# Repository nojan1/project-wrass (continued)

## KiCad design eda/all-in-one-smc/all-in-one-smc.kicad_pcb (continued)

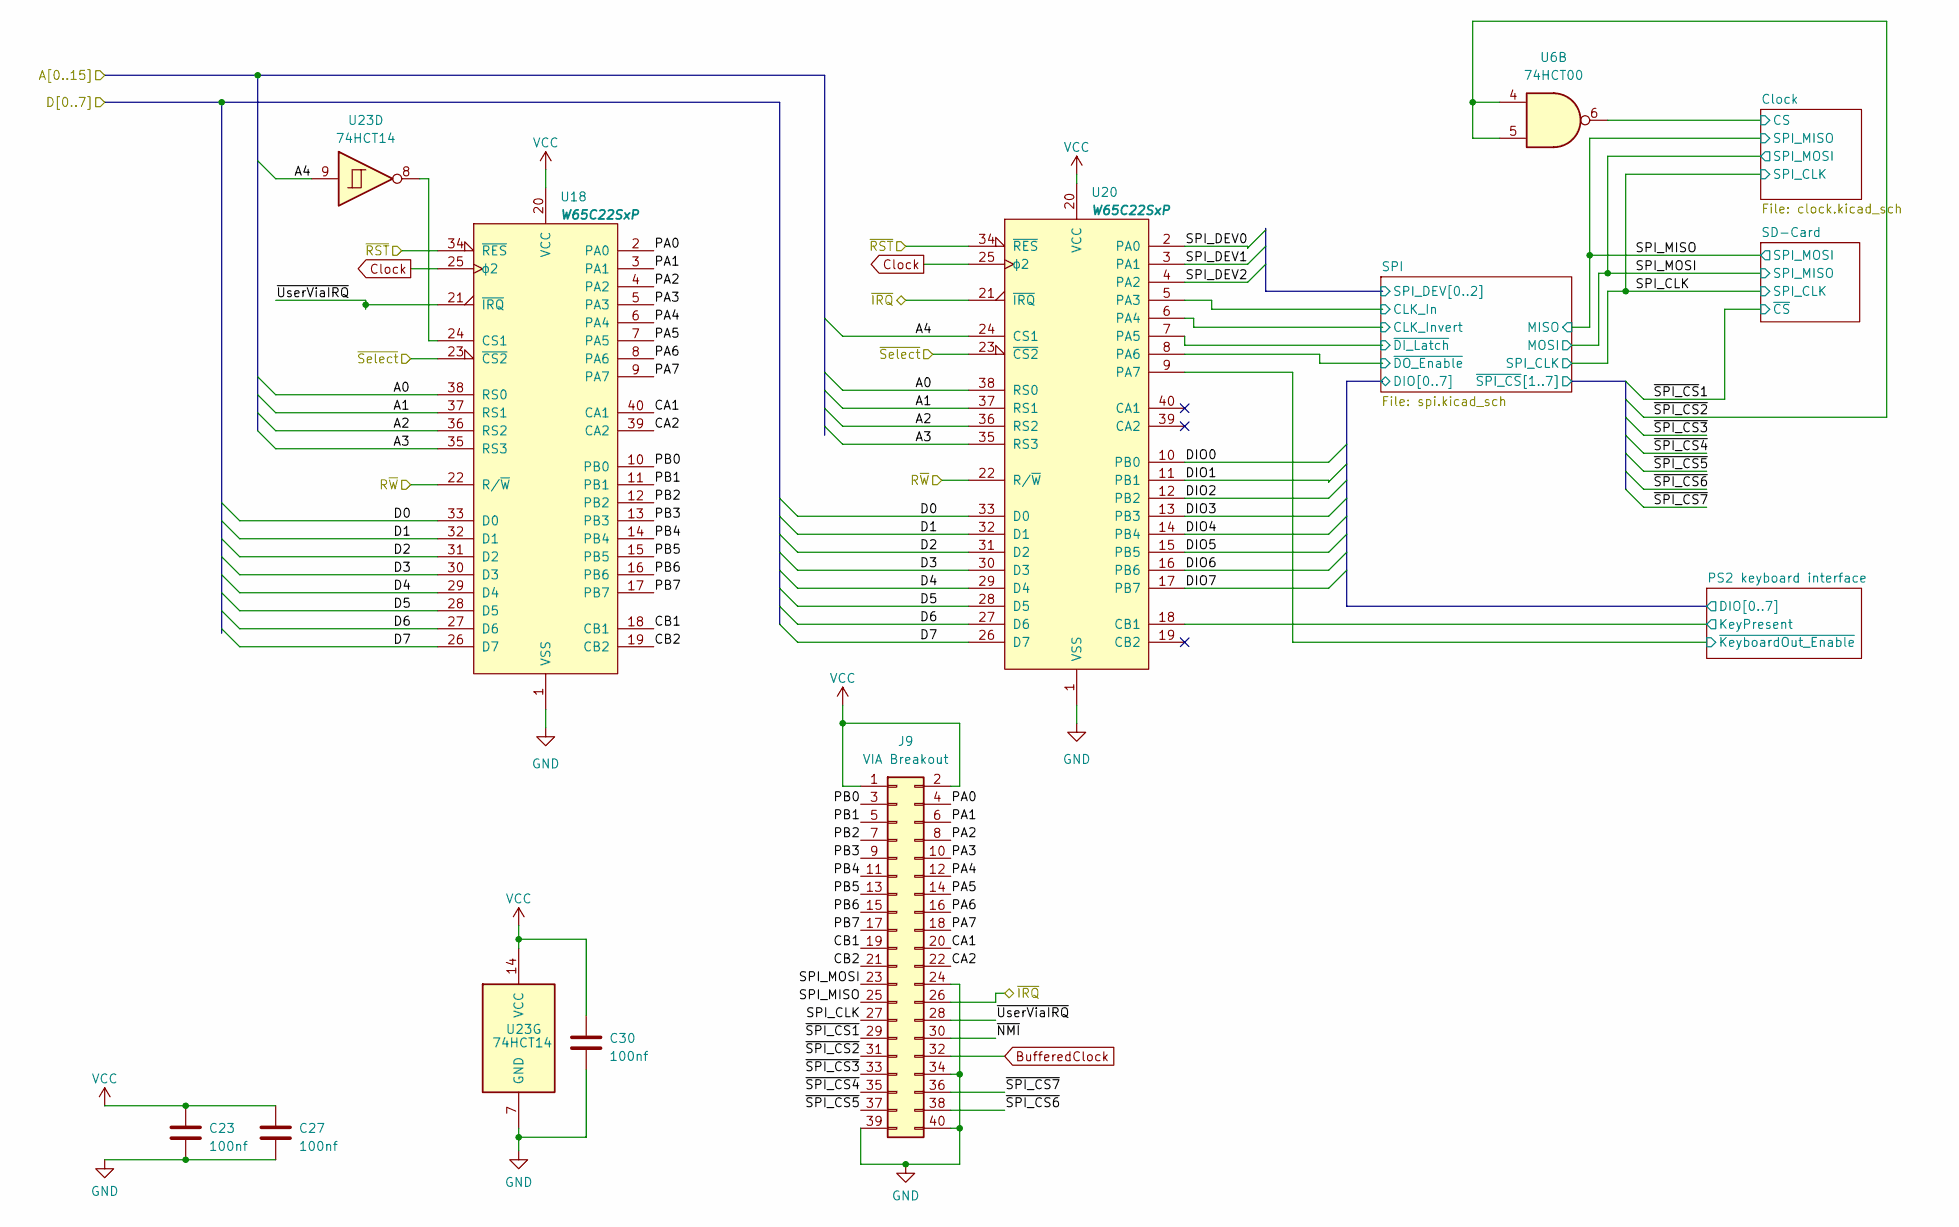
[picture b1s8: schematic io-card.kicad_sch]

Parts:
C23, C27, C30: 100nf; C_0805_2012Metric
J9: VIA Breakout; PinHeader_2x20_P2.54mm_Horizontal
U6: 74HCT00; SOIC-14_3.9x8.7mm_P1.27mm
U18, U20: W65C22SxP; PLCC-44_16.6x16.6mm_P1.27mm
U23: 74HCT14; SOIC-14_3.9x8.7mm_P1.27mm

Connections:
/A0: U18.38 (RS0), U20.38 (RS0); also elsewhere on the board
/A1: U18.37 (RS1), U20.37 (RS1); also elsewhere on the board
/A2: U18.36 (RS2), U20.36 (RS2); also elsewhere on the board
/A3: U18.35 (RS3), U20.35 (RS3); also elsewhere on the board
/A4: U20.24 (CS1), U23.9; also elsewhere on the board
/Address decode/R~W: U18.22 (R/~W), U20.22 (R/~W); also elsewhere on the board
/D0: U18.33 (D0), U20.33 (D0); also elsewhere on the board
/D1: U18.32 (D1), U20.32 (D1); also elsewhere on the board
/D2: U18.31 (D2), U20.31 (D2); also elsewhere on the board
/D3: U18.30 (D3), U20.30 (D3); also elsewhere on the board
/D4: U18.29 (D4), U20.29 (D4); also elsewhere on the board
/D5: U18.28 (D5), U20.28 (D5); also elsewhere on the board
/D6: U18.27 (D6), U20.27 (D6); also elsewhere on the board
/D7: U18.26 (D7), U20.26 (D7); also elsewhere on the board
/Expansion/IoSelect0: U18.23 (~CS2), U20.23 (~CS2); also elsewhere on the board
/Expansion/~IRQ: J9.26, U20.21 (~IRQ); also elsewhere on the board
/Expansion/~RST: U18.34 (~RES), U20.34 (~RES); also elsewhere on the board
/IO/CA1: J9.20, U18.40 (CA1)
/IO/CA2: J9.22, U18.39 (CA2)
/IO/CB1: J9.19, U18.18 (CB1)
/IO/CB2: J9.21, U18.19 (CB2)
/IO/Clock/CS: U6.6; also elsewhere on the board
/IO/PA2: J9.8, U18.4 (PA2)
/IO/PA5: J9.14, U18.7 (PA5)
/IO/PA6: J9.16, U18.8 (PA6)
/IO/PA7: J9.18, U18.9 (PA7)
/IO/PB3: J9.9, U18.13 (PB3)
/IO/PB6: J9.15, U18.16 (PB6)
/IO/PB7: J9.17, U18.17 (PB7)
/IO/PS2 keyboard interface/DIO0: U20.10 (PB0); also elsewhere on the board
/IO/PS2 keyboard interface/DIO1: U20.11 (PB1); also elsewhere on the board
/IO/PS2 keyboard interface/DIO2: U20.12 (PB2); also elsewhere on the board
/IO/PS2 keyboard interface/DIO3: U20.13 (PB3); also elsewhere on the board
/IO/PS2 keyboard interface/DIO4: U20.14 (PB4); also elsewhere on the board
/IO/PS2 keyboard interface/DIO5: U20.15 (PB5); also elsewhere on the board
/IO/PS2 keyboard interface/DIO6: U20.16 (PB6); also elsewhere on the board
/IO/PS2 keyboard interface/DIO7: U20.17 (PB7); also elsewhere on the board
/IO/PS2 keyboard interface/KeyPresent: U20.18 (CB1); also elsewhere on the board
/IO/PS2 keyboard interface/~KeyboardOut_Enable: U20.9 (PA7)
/IO/SPI/CLK_Invert: U20.6 (PA4); also elsewhere on the board
/IO/SPI/SPI_DEV0: U20.2 (PA0); also elsewhere on the board
/IO/SPI/SPI_DEV1: U20.3 (PA1); also elsewhere on the board
/IO/SPI/SPI_DEV2: U20.4 (PA2); also elsewhere on the board
/IO/SPI/~DI_Latch: U20.7 (PA5); also elsewhere on the board
/IO/SPI/~DO_Enable: U20.8 (PA6); also elsewhere on the board
/IO/SPI_CLK: J9.27, U20.5 (PA3); also elsewhere on the board
/IO/SPI_MISO: J9.25; also elsewhere on the board
/IO/SPI_MOSI: J9.23; also elsewhere on the board
/IO/~NMI: J9.30
/IO/~SPI_CS1: J9.29
/IO/~SPI_CS2: J9.31, U6.4, U6.5
/IO/~SPI_CS3: J9.33
/IO/~SPI_CS4: J9.35
/IO/~SPI_CS5: J9.37
/IO/~SPI_CS6: J9.38
/IO/~SPI_CS7: J9.36
/IO/~UserViaIRQ: J9.28, U18.21 (~IRQ)
BufferedClock: J9.32
Clock: U18.25 (ϕ2), U20.25 (ϕ2); also elsewhere on the board
unnamed: U18.24 (CS1), U23.8

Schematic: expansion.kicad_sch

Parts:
C18: 1u; CP_Elec_5x3
C20: 100n; C_0805_2012Metric
J6: Expansion; PinHeader_2x25_P2.54mm_Vertical
R7, R9, R10: 10k; R_0805_2012Metric
U13: 74HCT138; SOIC-16_3.9x9.9mm_P1.27mm

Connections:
/A0: J6.5; also elsewhere on the board
/A1: J6.7; also elsewhere on the board
/A2: J6.9; also elsewhere on the board
/A3: J6.11; also elsewhere on the board
/A4: J6.13; also elsewhere on the board
/A5: J6.15; also elsewhere on the board
/A6: J6.17, U13.1 (A0); also elsewhere on the board
/A7: J6.19, U13.2 (A1); also elsewhere on the board
/A8: J6.21, U13.3 (A2); also elsewhere on the board
/A9: J6.23; also elsewhere on the board
/A10: J6.25; also elsewhere on the board
/A11: J6.27; also elsewhere on the board
/A12: J6.29; also elsewhere on the board
/A13: J6.31; also elsewhere on the board
/A14: J6.33; also elsewhere on the board
/A15: J6.35; also elsewhere on the board
/Address decode/R~W: J6.41; also elsewhere on the board
/Address decode/~Io1Cs: U13.4 (E1), U13.5 (E2); also elsewhere on the board
/D0: J6.4; also elsewhere on the board
/D1: J6.6; also elsewhere on the board
/D2: J6.8; also elsewhere on the board
/D3: J6.10; also elsewhere on the board
/D4: J6.12; also elsewhere on the board
/D5: J6.14; also elsewhere on the board
/D6: J6.16; also elsewhere on the board
/D7: J6.18; also elsewhere on the board
/Expansion/IoSelect0: J6.22, U13.15 (O0); also elsewhere on the board
/Expansion/IoSelect1: J6.24, U13.14 (O1); also elsewhere on the board
/Expansion/IoSelect2: J6.26, U13.13 (O2)
/Expansion/IoSelect3: J6.28, U13.12 (O3); also elsewhere on the board
/Expansion/IoSelect4: J6.30, U13.11 (O4)
/Expansion/IoSelect5: J6.32, U13.10 (O5)
/Expansion/IoSelect6: J6.34, U13.9 (O6)
/Expansion/IoSelect7: J6.36, U13.7 (O7)
/Expansion/~DMA: J6.43, R7.2; also elsewhere on the board
/Expansion/~ExtRomCS: J6.48
/Expansion/~IRQ: J6.44, R10.2; also elsewhere on the board
/Expansion/~NMI: J6.42, R9.2; also elsewhere on the board
/Expansion/~RST: J6.40; also elsewhere on the board
Audio_GND: J6.47
Audio_L: J6.49
Audio_R: J6.45
Clock: J6.39; also elsewhere on the board

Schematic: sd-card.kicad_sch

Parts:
C44: 100nf; C_0805_2012Metric
C45: 100nf; CP_Elec_3x5.3
J11: SD-Card module; PinHeader_1x08_P2.54mm_Vertical
J12: SD_Card; SD_Kyocera_145638109511859+; not fitted
JP6: SD-Card voltage select; SolderJumper-3_P1.3mm_Open_Pad1.0x1.5mm
Q2, Q3, Q4, Q5: 2N7002; SOT-23
R30, R31, R32, R33, R34, R35, R36, R37: 10k; R_0805_2012Metric
R38: 370R; R_0805_2012Metric
R39: 220R; R_0805_2012Metric
U32: LM317L; SOT-223-3_TabPin2

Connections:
/IO/SPI/~SPI_CS1: Q2.3 (D), R34.2
/IO/SPI_CLK: Q4.3 (D), R36.2; also elsewhere on the board
/IO/SPI_MISO: Q3.3 (D), R35.2; also elsewhere on the board
/IO/SPI_MOSI: Q5.3 (D), R37.2; also elsewhere on the board
unnamed: J11.8, JP6.2 (C)
unnamed: R38.2, R39.1, U32.1 (ADJ)

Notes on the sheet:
VOUT = 1.25 * ( 1 + R2/R1 )
3.3 ~ 1.25 * ( 1 + 370/220 )

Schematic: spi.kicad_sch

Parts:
C38, C40, C41, C42, C43: 100nf; C_0805_2012Metric
J13: CS_Invert_Selection; PinHeader_2x03_P2.54mm_Horizontal
R40, R41, R42: 10k; R_0805_2012Metric
U23: 74HCT14; SOIC-14_3.9x8.7mm_P1.27mm
U24: 74HCT86; SOIC-14_3.9x8.7mm_P1.27mm
U26: 74HCT595; SOIC-16_3.9x9.9mm_P1.27mm
U27: 74HCT165; SOIC-16_3.9x9.9mm_P1.27mm
U31: 74HCT138; SOIC-16_3.9x9.9mm_P1.27mm

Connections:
/A4: U23.9; also elsewhere on the board
/IO/PS2 keyboard interface/DIO0: U26.7 (QH), U27.6 (D7); also elsewhere on the board
/IO/PS2 keyboard interface/DIO1: U26.6 (QG), U27.5 (D6); also elsewhere on the board
/IO/PS2 keyboard interface/DIO2: U26.5 (QF), U27.4 (D5); also elsewhere on the board
/IO/PS2 keyboard interface/DIO3: U26.4 (QE), U27.3 (D4); also elsewhere on the board
/IO/PS2 keyboard interface/DIO4: U26.3 (QD), U27.14 (D3); also elsewhere on the board
/IO/PS2 keyboard interface/DIO5: U26.2 (QC), U27.13 (D2); also elsewhere on the board
/IO/PS2 keyboard interface/DIO6: U26.1 (QB), U27.12 (D1); also elsewhere on the board
/IO/PS2 keyboard interface/DIO7: U26.15 (QA), U27.11 (D0); also elsewhere on the board
/IO/PS2 keyboard interface/KeyPresent: U23.6; also elsewhere on the board
/IO/PS2 keyboard interface/~KeyboardClk: U23.4; also elsewhere on the board
/IO/SPI/ ~SPI_CS1: U31.14 (O1)
/IO/SPI/CLK_Invert: U24.2; also elsewhere on the board
/IO/SPI/Conditioned_CLK: U23.13, U24.3, U26.11 (SRCLK)
/IO/SPI/SPI_DEV0: U31.1 (A0); also elsewhere on the board
/IO/SPI/SPI_DEV1: U31.2 (A1); also elsewhere on the board
/IO/SPI/SPI_DEV2: U31.3 (A2); also elsewhere on the board
/IO/SPI/~Conditioned_CLK: U23.12, U27.2 (CP)
/IO/SPI/~DI_Latch: U27.1 (~PL); also elsewhere on the board
/IO/SPI/~DO_Enable: U23.11, U26.13 (~OE); also elsewhere on the board
/IO/SPI/~SPI_CS2: U31.13 (O2)
/IO/SPI/~SPI_CS3: U31.12 (O3)
/IO/SPI/~SPI_CS4: U31.11 (O4)
/IO/SPI/~SPI_CS5: U24.6
/IO/SPI/~SPI_CS6: U24.8
/IO/SPI/~SPI_CS7: U24.11
/IO/SPI_CLK: U24.1; also elsewhere on the board
/IO/SPI_MISO: U26.14 (SER); also elsewhere on the board
/IO/SPI_MOSI: U27.9 (Q7); also elsewhere on the board
unnamed 158: U23.2; also elsewhere on the board
unnamed 159: U23.5; also elsewhere on the board
unnamed 165: U23.1, U23.3; also elsewhere on the board
unnamed: J13.1, R40.1, U24.13
unnamed: J13.3, R41.1, U24.10
unnamed: J13.5, R42.1, U24.5
unnamed 199: U23.8; also elsewhere on the board
unnamed: U23.10, U26.12 (RCLK)
unnamed: U24.4, U31.10 (O5)
unnamed: U24.9, U31.9 (O6)
unnamed: U24.12, U31.7 (O7)

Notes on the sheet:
Should these be swapped?

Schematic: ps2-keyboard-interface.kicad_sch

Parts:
C36, C37, C39: 100nf; C_0805_2012Metric
D3: 1N457; D_0805_2012Metric
J10: PS2; Connector_Mini-DIN_Female_6Pin_2rows
R29: 33k; R_0805_2012Metric
U23: 74HCT14; SOIC-14_3.9x8.7mm_P1.27mm
U29, U30: 74HCT595; SOIC-16_3.9x9.9mm_P1.27mm

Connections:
/IO/PS2 keyboard interface/DIO0: U29.1 (QB); also elsewhere on the board
/IO/PS2 keyboard interface/DIO1: U29.2 (QC); also elsewhere on the board
/IO/PS2 keyboard interface/DIO2: U29.3 (QD); also elsewhere on the board
/IO/PS2 keyboard interface/DIO3: U29.4 (QE); also elsewhere on the board
/IO/PS2 keyboard interface/DIO4: U29.5 (QF); also elsewhere on the board
/IO/PS2 keyboard interface/DIO5: U29.6 (QG); also elsewhere on the board
/IO/PS2 keyboard interface/DIO6: U29.7 (QH); also elsewhere on the board
/IO/PS2 keyboard interface/KeyPresent: U23.6, U29.12 (RCLK), U30.12 (RCLK); also elsewhere on the board
/IO/PS2 keyboard interface/KeyboardBit7: U30.15 (QA)
/IO/PS2 keyboard interface/KeyboardData: J10.1, U29.14 (SER)
/IO/PS2 keyboard interface/~KeyboardClk: U23.4, U29.11 (SRCLK), U30.11 (SRCLK)
/IO/PS2 keyboard interface/~PS2ShiftOE: U29.13 (~OE), U30.13 (~OE); also elsewhere on the board
unnamed: D3.2 (A), R29.2, U23.2
unnamed: C39.1, D3.1 (K), R29.1, U23.5
unnamed: J10.5, U23.1, U23.3
unnamed: U29.9 (QH'), U30.14 (SER)

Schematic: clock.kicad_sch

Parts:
BT1: CR2032; Battery_Panasonic_CR2032-HFN_Horizontal_CircularHoles
C46, C47: 6pf; C_0805_2012Metric
U100: DS1306; TSSOP-20_4.4x5mm_P0.4mm
Y3: 32.768kHz; Crystal_C26-LF_D2.1mm_L6.5mm_Vertical

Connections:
/IO/Clock/CS: U100.12 (CE); also elsewhere on the board
/IO/SPI_CLK: U100.14 (SCLK); also elsewhere on the board
/IO/SPI_MISO: U100.16 (SDO); also elsewhere on the board
/IO/SPI_MOSI: U100.15 (SDI); also elsewhere on the board
unnamed: BT1.1 (+), U100.2 (VBAT)
unnamed: C46.2, U100.3 (X1), Y3.2
unnamed: C47.2, U100.5 (X2), Y3.1

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
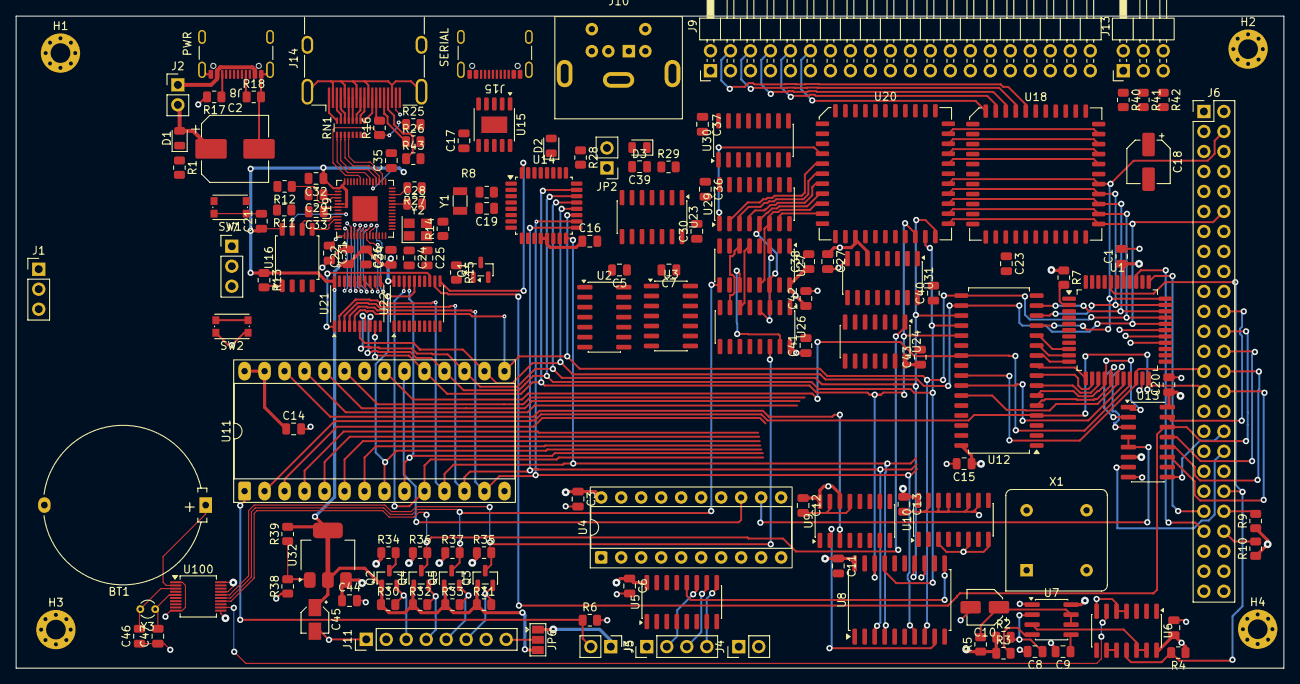
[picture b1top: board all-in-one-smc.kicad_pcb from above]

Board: 4 copper layers, 161.1 x 82.9 mm, 150 parts (0 on the bottom side), 210 nets.

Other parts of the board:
JP2: Enable PS2 Output; PinHeader_1x02_P2.54mm_Vertical
R28: 10k; R_0805_2012Metric

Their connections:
/IO/PS2 keyboard interface/~PS2ShiftOE: JP2.1 (A), R28.2; also elsewhere on the board

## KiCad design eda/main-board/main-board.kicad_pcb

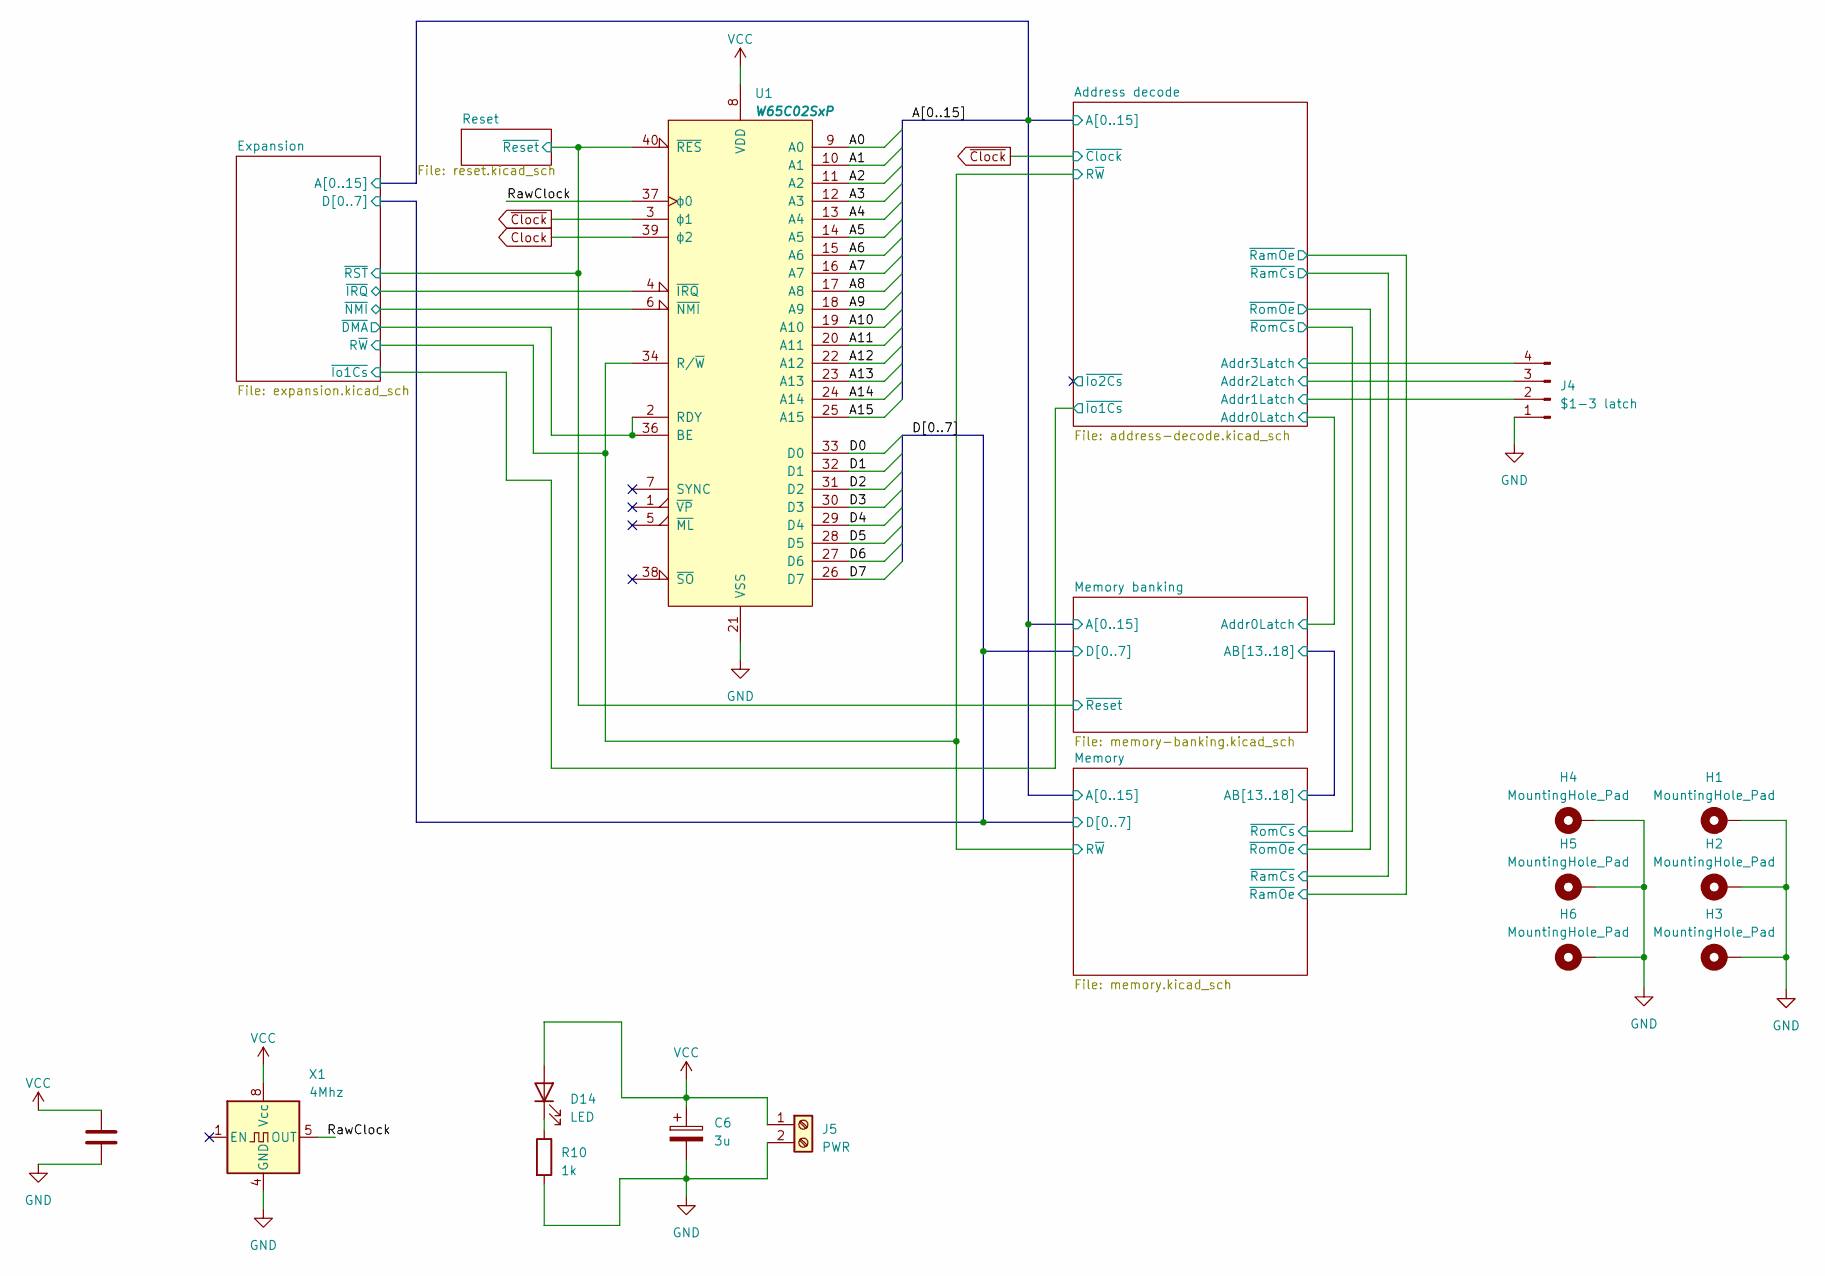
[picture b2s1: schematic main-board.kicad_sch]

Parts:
C4: 100n; C_Disc_D3.8mm_W2.6mm_P2.50mm
C6: 3u; CP_Radial_D8.0mm_P3.50mm
D14: LED; LED_D3.0mm
H1, H2, H3, H4, H5, H6: MountingHole_Pad; MountingHole_2.5mm_Pad_Via
J4: $1-3 latch; PinHeader_1x04_P2.54mm_Vertical
J5: PWR; TerminalBlock_Altech_AK300-2_P5.00mm
R10: 1k; R_Axial_DIN0207_L6.3mm_D2.5mm_P7.62mm_Horizontal
U1: W65C02SxP; DIP-40_W15.24mm
X1: 4Mhz; Oscillator_DIP-8

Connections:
/A0: U1.9 (A0); also elsewhere on the board
/A1: U1.10 (A1); also elsewhere on the board
/A2: U1.11 (A2); also elsewhere on the board
/A3: U1.12 (A3); also elsewhere on the board
/A4: U1.13 (A4); also elsewhere on the board
/A5: U1.14 (A5); also elsewhere on the board
/A6: U1.15 (A6); also elsewhere on the board
/A7: U1.16 (A7); also elsewhere on the board
/A8: U1.17 (A8); also elsewhere on the board
/A9: U1.18 (A9); also elsewhere on the board
/A10: U1.19 (A10); also elsewhere on the board
/A11: U1.20 (A11); also elsewhere on the board
/A12: U1.22 (A12); also elsewhere on the board
/A13: U1.23 (A13); also elsewhere on the board
/A14: U1.24 (A14); also elsewhere on the board
/A15: U1.25 (A15); also elsewhere on the board
/Address decode/Addr1Latch: J4.2; also elsewhere on the board
/Address decode/Addr2Latch: J4.3; also elsewhere on the board
/Address decode/Addr3Latch: J4.4; also elsewhere on the board
/Address decode/R~W: U1.34 (R/~W); also elsewhere on the board
/D0: U1.33 (D0); also elsewhere on the board
/D1: U1.32 (D1); also elsewhere on the board
/D2: U1.31 (D2); also elsewhere on the board
/D3: U1.30 (D3); also elsewhere on the board
/D4: U1.29 (D4); also elsewhere on the board
/D5: U1.28 (D5); also elsewhere on the board
/D6: U1.27 (D6); also elsewhere on the board
/D7: U1.26 (D7); also elsewhere on the board
/Expansion/~DMA: U1.2 (RDY), U1.36 (BE); also elsewhere on the board
/Expansion/~IRQ: U1.4 (~IRQ); also elsewhere on the board
/Expansion/~NMI: U1.6 (~NMI); also elsewhere on the board
/Expansion/~RST: U1.40 (~RES); also elsewhere on the board
/RawClock: U1.37 (ϕ0), X1.5 (OUT)
Clock: U1.39 (ϕ2); also elsewhere on the board
GND: C4.2, C6.2, H1.1, H2.1, H3.1, H4.1, H5.1, H6.1, J4.1, J5.2, R10.2, U1.21 (VSS), X1.4 (GND); also elsewhere on the board
unnamed: D14.1 (K), R10.1
VCC: C4.1, C6.1, D14.2 (A), J5.1, U1.8 (VDD), X1.8 (Vcc); also elsewhere on the board
~Clock: U1.3 (ϕ1); also elsewhere on the board

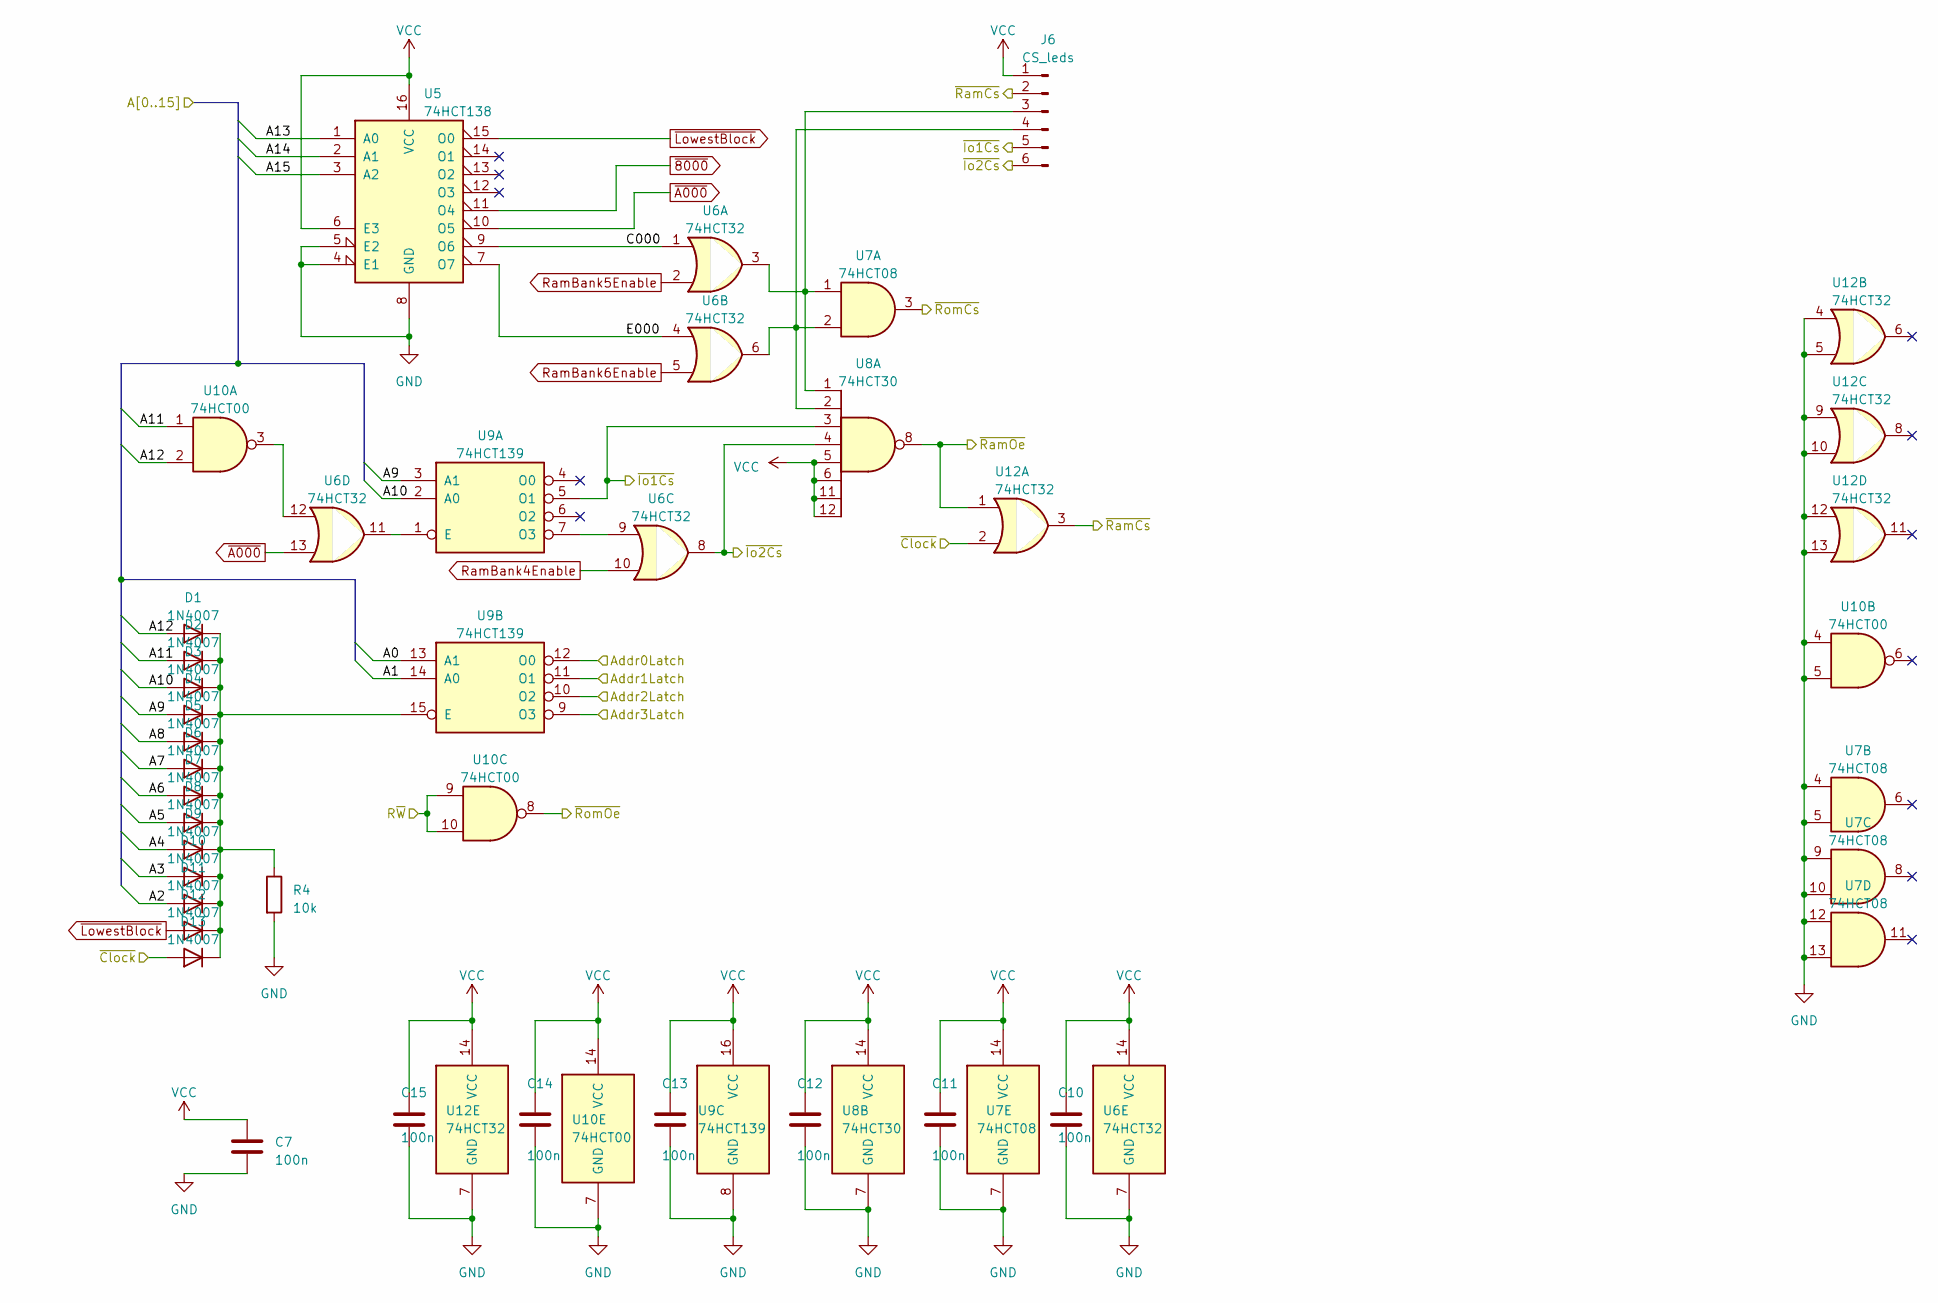
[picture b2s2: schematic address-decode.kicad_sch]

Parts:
C7, C10, C11, C12, C13, C14, C15: 100n; C_Disc_D3.8mm_W2.6mm_P2.50mm
D1, D2, D3, D4, D5, D6, D7, D8, D9, D10, D11, D12, D13: 1N4007; D_DO-41_SOD81_P7.62mm_Horizontal
J6: CS_leds; PinHeader_1x06_P2.54mm_Vertical
R4: 10k; R_Axial_DIN0207_L6.3mm_D2.5mm_P7.62mm_Horizontal
U5: 74HCT138; DIP-16_W7.62mm
U6, U12: 74HCT32; DIP-14_W7.62mm
U7: 74HCT08; DIP-14_W7.62mm
U8: 74HCT30; DIP-14_W7.62mm
U9: 74HCT139; DIP-16_W7.62mm
U10: 74HCT00; DIP-14_W7.62mm

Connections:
/A0: U9.13 (A1); also elsewhere on the board
/A1: U9.14 (A0); also elsewhere on the board
/A2: D11.2 (A); also elsewhere on the board
/A3: D10.2 (A); also elsewhere on the board
/A4: D9.2 (A); also elsewhere on the board
/A5: D8.2 (A); also elsewhere on the board
/A6: D7.2 (A); also elsewhere on the board
/A7: D6.2 (A); also elsewhere on the board
/A8: D5.2 (A); also elsewhere on the board
/A9: D4.2 (A), U9.3 (A1); also elsewhere on the board
/A10: D3.2 (A), U9.2 (A0); also elsewhere on the board
/A11: D2.2 (A), U10.1; also elsewhere on the board
/A12: D1.2 (A), U10.2; also elsewhere on the board
/A13: U5.1 (A0); also elsewhere on the board
/A14: U5.2 (A1); also elsewhere on the board
/A15: U5.3 (A2); also elsewhere on the board
/Address decode/Addr0Latch: U9.12 (O0); also elsewhere on the board
/Address decode/Addr1Latch: U9.11 (O1); also elsewhere on the board
/Address decode/Addr2Latch: U9.10 (O2); also elsewhere on the board
/Address decode/Addr3Latch: U9.9 (O3); also elsewhere on the board
/Address decode/C000: U5.9 (O6), U6.1
/Address decode/E000: U5.7 (O7), U6.4
/Address decode/R~W: U10.9, U10.10; also elsewhere on the board
/Address decode/~Io1Cs: J6.5, U8.3, U9.5 (O1); also elsewhere on the board
/Address decode/~Io2Cs: J6.6, U6.8, U8.4
/Address decode/~RamCs: J6.2, U12.3; also elsewhere on the board
/Address decode/~RamOe: U8.8, U12.1; also elsewhere on the board
/Address decode/~RomCs: U7.3; also elsewhere on the board
/Address decode/~RomOe: U10.8; also elsewhere on the board
GND: C7.2, C10.2, C11.2, C12.2, C13.2, C14.2, C15.2, R4.2, U5.4 (E1), U5.5 (E2), U5.8 (GND), U6.7 (GND), U7.4, U7.5, U7.7 (GND), U7.9, U7.10, U7.12, U7.13, U8.7 (GND), U9.8 (GND), U10.4, U10.5, U10.7 (GND), U12.4, U12.5, U12.7 (GND), U12.9, U12.10, U12.12, U12.13; also elsewhere on the board
unnamed: D1.1 (K), D2.1 (K), D3.1 (K), D4.1 (K), D5.1 (K), D6.1 (K), D7.1 (K), D8.1 (K), D9.1 (K), D10.1 (K), D11.1 (K), D12.1 (K), D13.1 (K), R4.1, U9.15 (E)
unnamed: J6.3, U6.3, U7.1, U8.1
unnamed: J6.4, U6.6, U7.2, U8.2
unnamed: U6.11, U9.1 (E)
unnamed: U6.9, U9.7 (O3)
unnamed: U6.12, U10.3
RamBank4Enable: U6.10; also elsewhere on the board
RamBank5Enable: U6.2; also elsewhere on the board
RamBank6Enable: U6.5; also elsewhere on the board
VCC: C7.1, C10.1, C11.1, C12.1, C13.1, C14.1, C15.1, J6.1, U5.6 (E3), U5.16 (VCC), U6.14 (VCC), U7.14 (VCC), U8.5, U8.6, U8.11, U8.12, U8.14 (VCC), U9.16 (VCC), U10.14 (VCC), U12.14 (VCC); also elsewhere on the board
~8000: U5.11 (O4); also elsewhere on the board
~A000: U5.10 (O5), U6.13
~Clock: D13.2 (A), U12.2; also elsewhere on the board
~LowestBlock: D12.2 (A), U5.15 (O0)

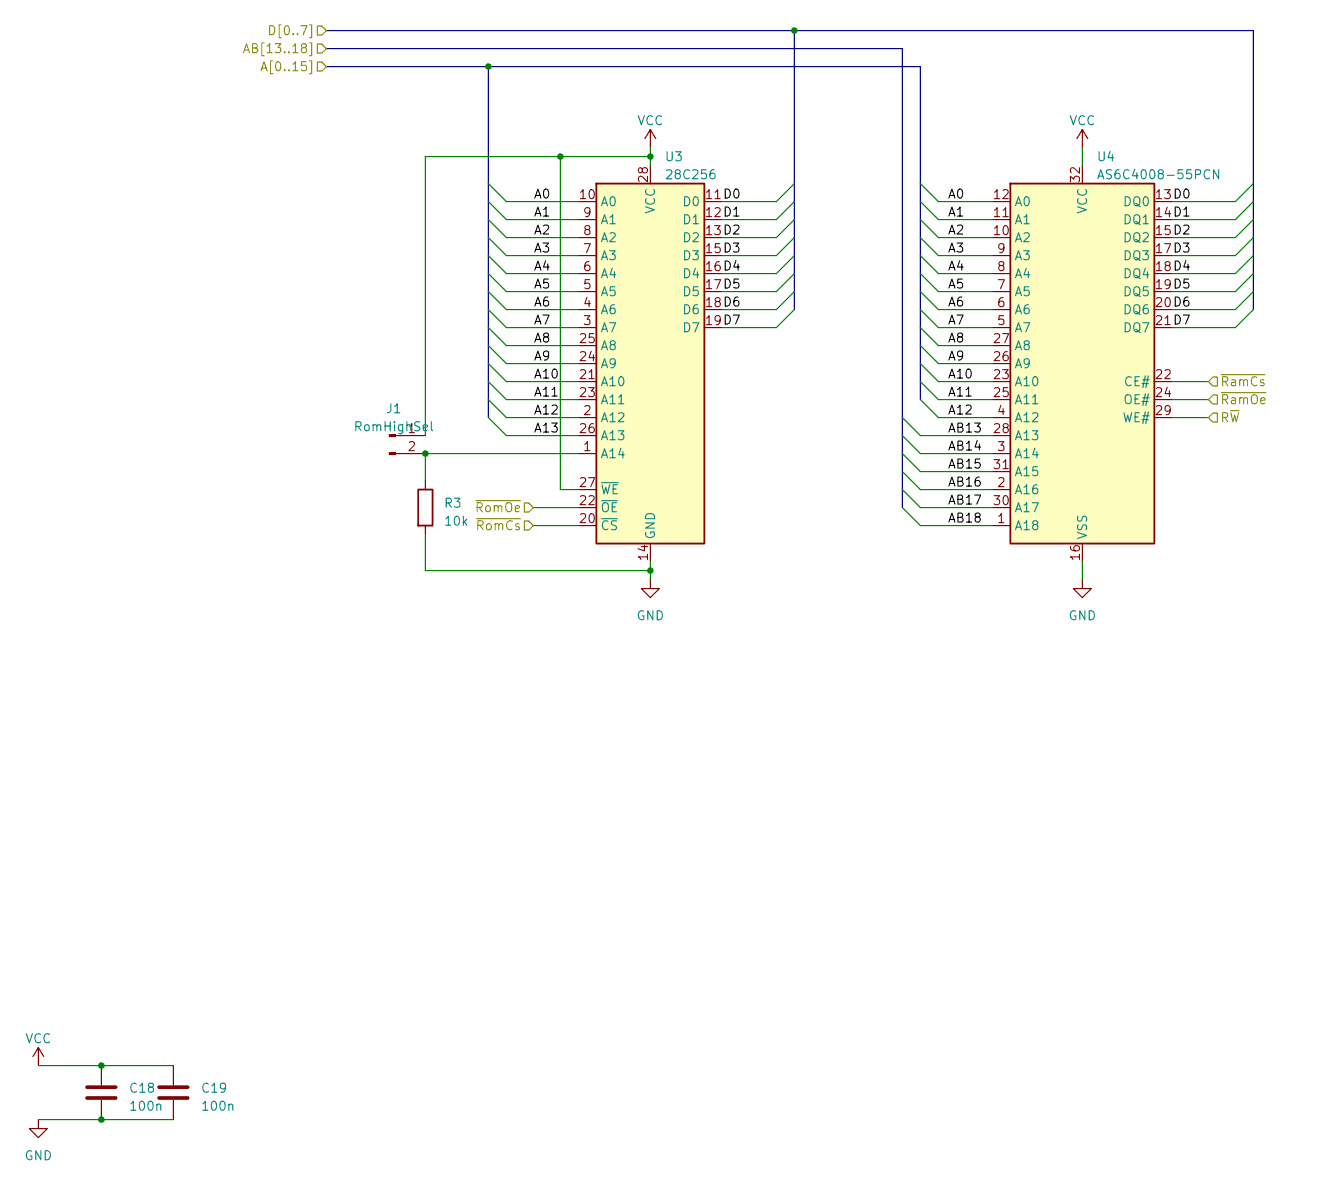
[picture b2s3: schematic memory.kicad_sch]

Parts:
C18, C19: 100n; C_Disc_D3.8mm_W2.6mm_P2.50mm
J1: RomHighSel; PinHeader_1x02_P2.54mm_Vertical
R3: 10k; R_Axial_DIN0207_L6.3mm_D2.5mm_P7.62mm_Horizontal
U3: 28C256; DIP_Socket-28_W11.9_W12.7_W15.24_W17.78_W18.5_3M_228-1277-0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
U4: AS6C4008-55PCN; DIP-32_W15.24mm

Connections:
/A0: U3.10 (A0), U4.12 (A0); also elsewhere on the board
/A1: U3.9 (A1), U4.11 (A1); also elsewhere on the board
/A2: U3.8 (A2), U4.10 (A2); also elsewhere on the board
/A3: U3.7 (A3), U4.9 (A3); also elsewhere on the board
/A4: U3.6 (A4), U4.8 (A4); also elsewhere on the board
/A5: U3.5 (A5), U4.7 (A5); also elsewhere on the board
/A6: U3.4 (A6), U4.6 (A6); also elsewhere on the board
/A7: U3.3 (A7), U4.5 (A7); also elsewhere on the board
/A8: U3.25 (A8), U4.27 (A8); also elsewhere on the board
/A9: U3.24 (A9), U4.26 (A9); also elsewhere on the board
/A10: U3.21 (A10), U4.23 (A10); also elsewhere on the board
/A11: U3.23 (A11), U4.25 (A11); also elsewhere on the board
/A12: U3.2 (A12), U4.4 (A12); also elsewhere on the board
/A13: U3.26 (A13); also elsewhere on the board
/Address decode/R~W: U4.29 (WE#); also elsewhere on the board
/Address decode/~RamCs: U4.22 (CE#); also elsewhere on the board
/Address decode/~RamOe: U4.24 (OE#); also elsewhere on the board
/Address decode/~RomCs: U3.20 (~CS); also elsewhere on the board
/Address decode/~RomOe: U3.22 (~OE); also elsewhere on the board
/D0: U3.11 (D0), U4.13 (DQ0); also elsewhere on the board
/D1: U3.12 (D1), U4.14 (DQ1); also elsewhere on the board
/D2: U3.13 (D2), U4.15 (DQ2); also elsewhere on the board
/D3: U3.15 (D3), U4.17 (DQ3); also elsewhere on the board
/D4: U3.16 (D4), U4.18 (DQ4); also elsewhere on the board
/D5: U3.17 (D5), U4.19 (DQ5); also elsewhere on the board
/D6: U3.18 (D6), U4.20 (DQ6); also elsewhere on the board
/D7: U3.19 (D7), U4.21 (DQ7); also elsewhere on the board
/Memory banking/AB13: U4.28 (A13); also elsewhere on the board
/Memory banking/AB14: U4.3 (A14); also elsewhere on the board
/Memory banking/AB15: U4.31 (A15); also elsewhere on the board
/Memory banking/AB16: U4.2 (A16); also elsewhere on the board
/Memory banking/AB17: U4.30 (A17); also elsewhere on the board
/Memory banking/AB18: U4.1 (A18); also elsewhere on the board
GND: C18.2, C19.2, R3.2, U3.14 (GND), U4.16 (VSS); also elsewhere on the board
unnamed: J1.2, R3.1, U3.1 (A14)
VCC: C18.1, C19.1, J1.1, U3.27 (~WE), U3.28 (VCC), U4.32 (VCC); also elsewhere on the board

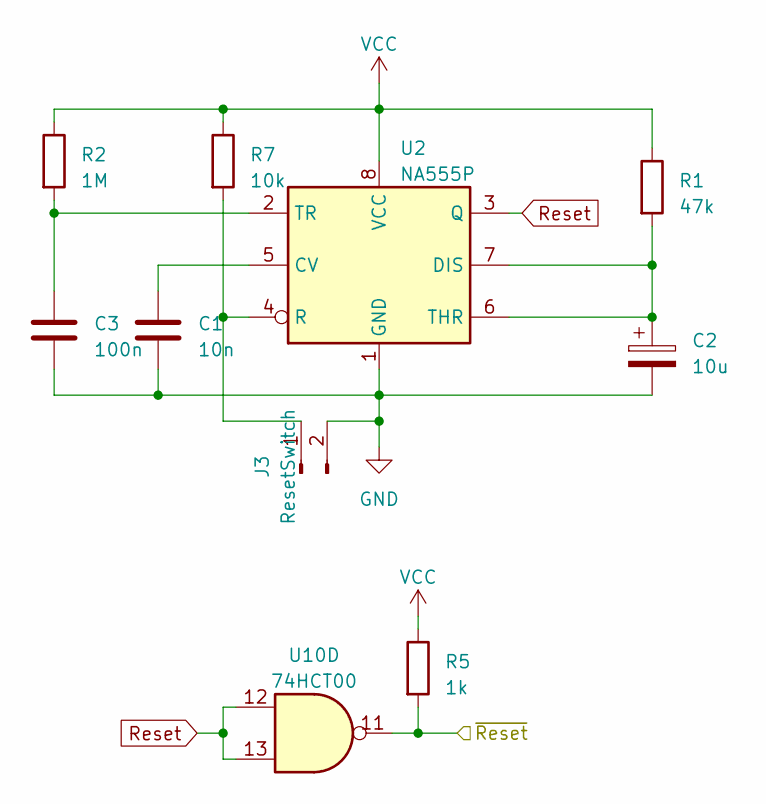
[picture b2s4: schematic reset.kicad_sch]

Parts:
C1: 10n; C_Disc_D6.0mm_W2.5mm_P5.00mm
C2: 10u; CP_Radial_D4.0mm_P1.50mm
C3: 100n; C_Disc_D3.8mm_W2.6mm_P2.50mm
J3: ResetSwitch; PinHeader_1x02_P2.54mm_Vertical
R1: 47k; R_Axial_DIN0207_L6.3mm_D2.5mm_P7.62mm_Horizontal
R2: 1M; R_Axial_DIN0207_L6.3mm_D2.5mm_P7.62mm_Horizontal
R5: 1k; R_Axial_DIN0207_L6.3mm_D2.5mm_P7.62mm_Horizontal
R7: 10k; R_Axial_DIN0207_L6.3mm_D2.5mm_P7.62mm_Horizontal
U2: NA555P; DIP-8_W7.62mm
U10: 74HCT00; DIP-14_W7.62mm

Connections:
/Expansion/~RST: R5.2, U10.11; also elsewhere on the board
GND: C1.2, C2.2, C3.2, J3.2, U2.1 (GND); also elsewhere on the board
unnamed: J3.1, R7.2, U2.4 (R)
unnamed: C1.1, U2.5 (CV)
unnamed: C2.1, R1.2, U2.6 (THR), U2.7 (DIS)
unnamed: C3.1, R2.2, U2.2 (TR)
Reset: U2.3 (Q), U10.12, U10.13
VCC: R1.1, R2.1, R5.1, R7.1, U2.8 (VCC); also elsewhere on the board
